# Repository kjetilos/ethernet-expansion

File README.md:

# ethernet-expansion
An ethernet expansion board using the enc28j60 chip

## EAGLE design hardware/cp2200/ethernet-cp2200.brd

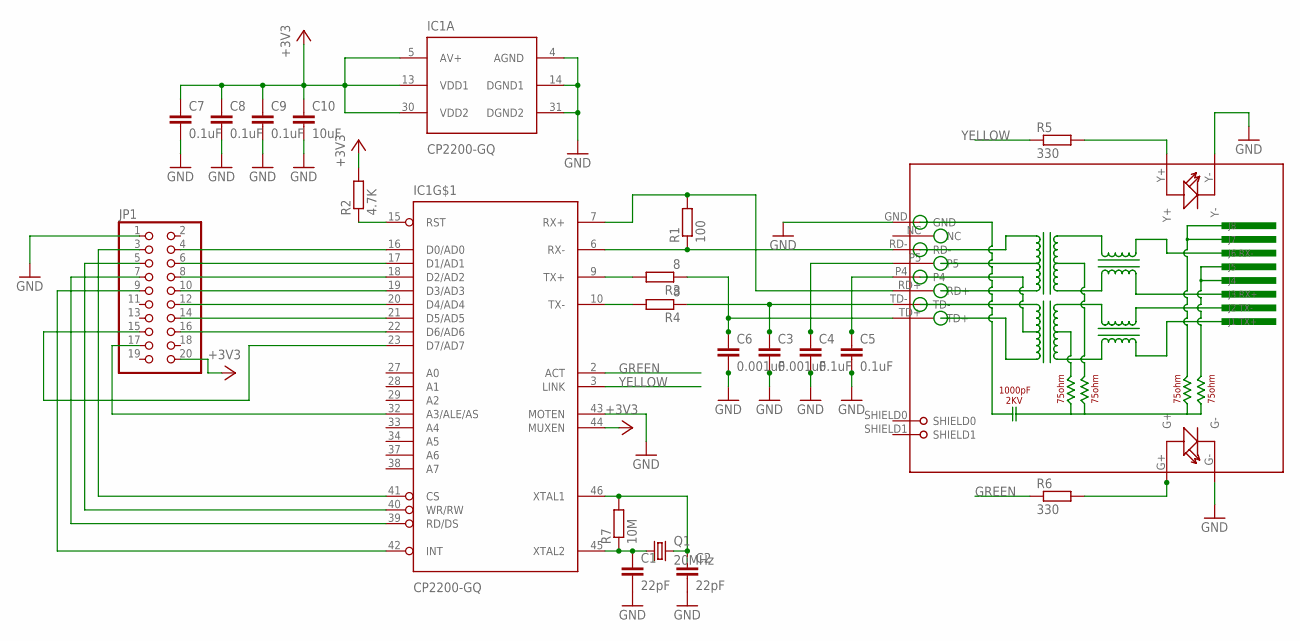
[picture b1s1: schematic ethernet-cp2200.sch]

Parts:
C1, C2: 22pF; C0805
C3, C6: 0.001uF; C0805
C4, C5, C7, C8, C9: 0.1uF; C0805
C10: 10uF; C0805
IC1: CP2200-GQ; TQFP-48
JP1: PINHD-2X10; 2X10
Q1: 20MHz; HC49/S
R1: 100; M0805
R2: 4.7K; M0805
R3, R4: 8; M0805
R5, R6: 330; M0805
R7: 10M; M0805
RJ1: HR911105A

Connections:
+3V3: C7.1, C8.1, C9.1, C10.1, IC1.5 (AV+), IC1.13 (VDD1), IC1.30 (VDD2), IC1.44 (MUXEN), JP1.20, R2.2
GND: C1.2, C2.2, C3.2, C4.2, C5.2, C6.2, C7.2, C8.2, C9.2, C10.2, IC1.4 (AGND), IC1.14 (DGND1), IC1.31 (DGND2), IC1.43 (MOTEN), JP1.1, RJ1.G-, RJ1.GND, RJ1.Y-
GREEN: IC1.2 (ACT), R6.1
unnamed: C2.1, IC1.46 (XTAL1), Q1.2, R7.2
unnamed: C1.1, IC1.45 (XTAL2), Q1.1, R7.1
unnamed: IC1.6 (RX-), R1.1, RJ1.RD-
unnamed: IC1.7 (RX+), R1.2, RJ1.RD+
unnamed: IC1.9 (TX+), R3.2
unnamed: C6.1, R3.1, RJ1.TD+
unnamed: IC1.10 (TX-), R4.2
unnamed: R5.2, RJ1.Y+
unnamed: R6.2, RJ1.G+
unnamed: IC1.32 (A3/ALE/AS), JP1.17
unnamed: C3.1, R4.1, RJ1.TD-
unnamed: IC1.16 (D0/AD0), JP1.4
unnamed: C5.1, RJ1.P4
unnamed: C4.1, RJ1.P5
unnamed: IC1.17 (D1/AD1), JP1.6
unnamed: IC1.18 (D2/AD2), JP1.8
unnamed: IC1.19 (D3/AD3), JP1.10
unnamed: IC1.20 (D4/AD4), JP1.12
unnamed: IC1.21 (D5/AD5), JP1.14
unnamed: IC1.22 (D6/AD6), JP1.16
unnamed: IC1.23 (D7/AD7), JP1.15
unnamed: IC1.41 (CS), JP1.3
unnamed: IC1.40 (WR/RW), JP1.5
unnamed: IC1.39 (RD/DS), JP1.7
unnamed: IC1.42 (INT), JP1.9
unnamed: IC1.15 (RST), R2.1
YELLOW: IC1.3 (LINK), R5.1

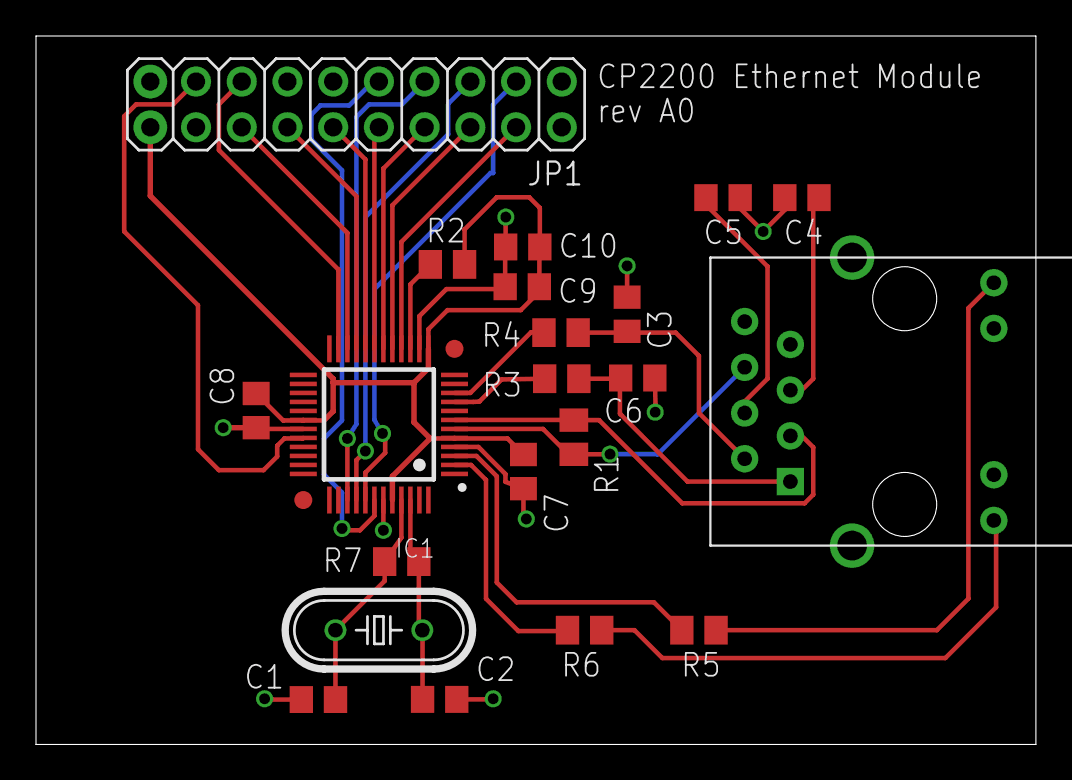
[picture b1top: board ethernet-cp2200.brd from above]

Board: 2 copper layers, 55.5 x 39.4 mm, 21 parts (0 on the bottom side), 30 nets.

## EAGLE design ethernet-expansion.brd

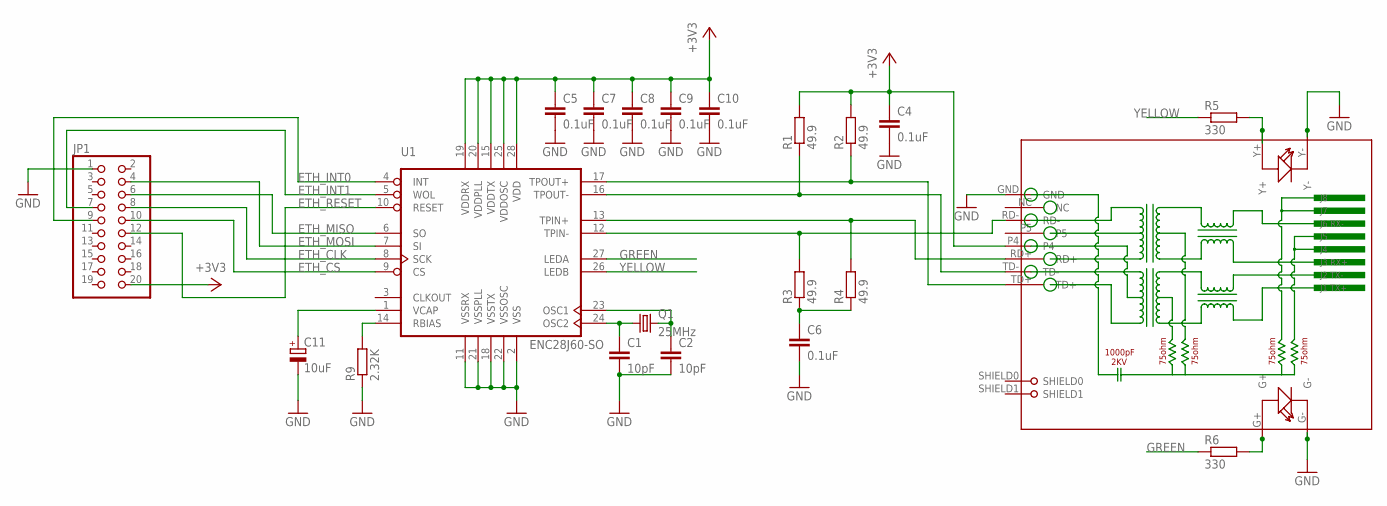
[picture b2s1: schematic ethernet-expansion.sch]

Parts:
C1, C2: 10pF; C0805
C4, C5, C6, C7, C8, C9, C10: 0.1uF; C0805
C11: 10uF; E2-4
JP1: PINHD-2X10; 2X10
Q1: 25MHz; HC49/S
R1, R2, R3, R4: 49.9; M0805
R5, R6: 330; M0805
R9: 2.32K; M0805
RJ1: HR911105A
U1: ENC28J60-SO; SO28W

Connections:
+3V3: C4.1, C5.1, C7.1, C8.1, C9.1, C10.1, JP1.20, R1.2, R2.2, RJ1.P4, U1.15 (VDDTX), U1.19 (VDDRX), U1.20 (VDDPLL), U1.25 (VDDOSC), U1.28 (VDD)
ETH_CLK: JP1.8, U1.8 (SCK)
ETH_CS: JP1.10, U1.9 (CS)
ETH_INT0: JP1.9, U1.4 (INT)
ETH_INT1: JP1.7, U1.5 (WOL)
ETH_MISO: JP1.6, U1.6 (SO)
ETH_MOSI: JP1.4, U1.7 (SI)
ETH_RESET: JP1.12, U1.10 (RESET)
GND: C1.2, C2.2, C4.2, C5.2, C6.2, C7.2, C8.2, C9.2, C10.2, C11.-, JP1.1, R9.1, RJ1.G-, RJ1.GND, RJ1.Y-, U1.2 (VSS), U1.11 (VSSRX), U1.18 (VSSTX), U1.21 (VSSPLL), U1.22 (VSSOSC)
GREEN: R6.1, U1.27 (LEDA)
unnamed: C6.1, R3.1, R4.1
unnamed: R5.2, RJ1.Y+
unnamed: R6.2, RJ1.G+
unnamed: C1.1, Q1.1, U1.24 (OSC2)
unnamed: C2.1, Q1.2, U1.23 (OSC1)
unnamed: R9.2, U1.14 (RBIAS)
unnamed: C11.+, U1.1 (VCAP)
TPIN_N: R3.2, RJ1.RD-, U1.12 (TPIN-)
TPIN_P: R4.2, RJ1.RD+, U1.13 (TPIN+)
TPOUT_N: R1.1, RJ1.TD-, U1.16 (TPOUT-)
TPOUT_P: R2.1, RJ1.TD+, U1.17 (TPOUT+)
YELLOW: R5.1, U1.26 (LEDB)

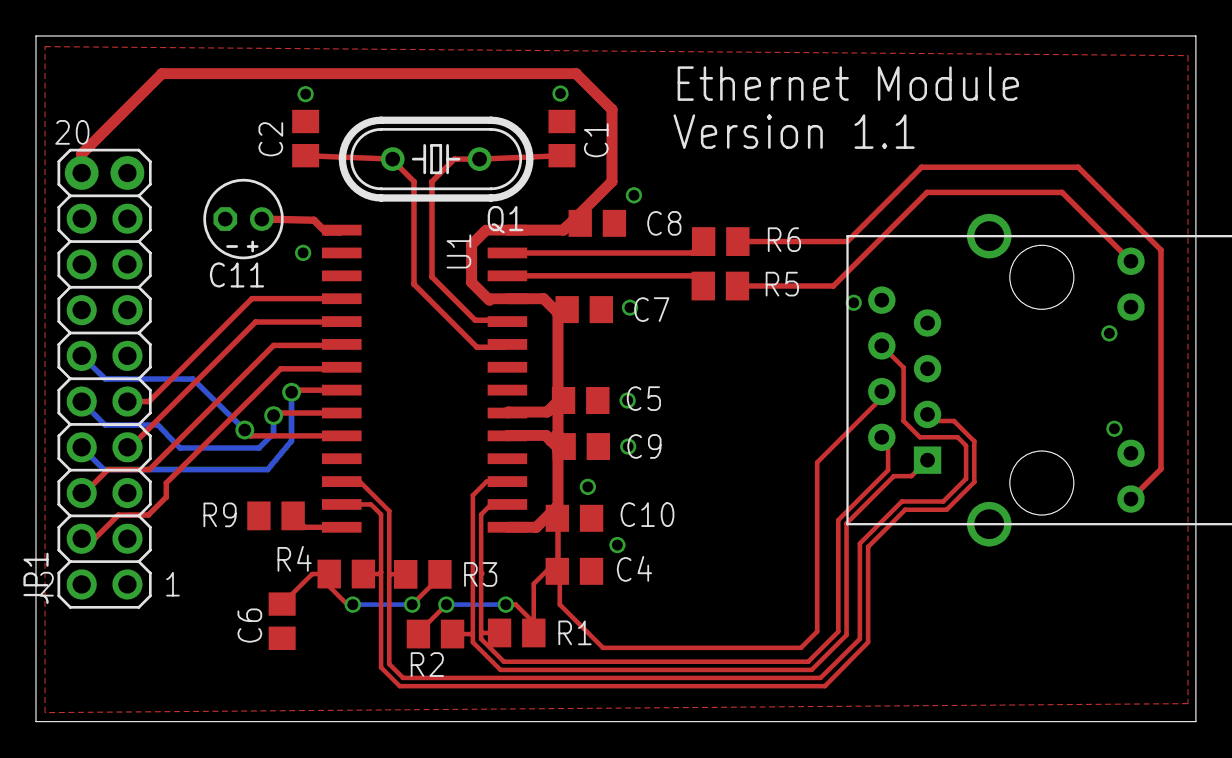
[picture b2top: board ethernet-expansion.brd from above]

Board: 2 copper layers, 64.4 x 38.1 mm, 21 parts (0 on the bottom side), 22 nets.

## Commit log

2015-08-04 Adding the initial schematic and board layout
2015-08-04 Adding notes and gitignore
2015-08-29 Add center tap connection and interrupt connections
2015-09-01 Started to route the connector
2015-09-02 Initial board with all wires routed
2015-09-02 Adding some text
2015-09-02 Rotated oscillator to get a better Vdd trace
2015-09-05 Adding ground fill on top layer and trying out other placements
2015-09-05 Canged signal trace with from 0.1 to 0.3
2015-09-06 Routed differential pairs and fixed most of the drc errors
2015-09-06 Added some silk screen and added osh park eagle design rule file
2015-09-06 Recreated the ground fill to fix the last error
2015-09-07 Adding dru and cam file from Seeed studio and moving traces to make the ground fill more complete
2015-09-10 Adding ground plane on bottom layer and vias at ground points
2015-10-03 Swapping header pin rows to make it correct, and adding debug uart pins
2015-10-03 Adding image of board and schematic
2015-10-29 Adding software for the ethernet expansion card
2015-10-29 Moving stk specific config to another folder
2015-11-08 Adding support for blocking socket operations and support for frames divided into multiple pbuf's
2015-11-09 Adding support for displaying a text on the STK3700 lcd display
2016-01-04 Adding board and schematic for cp2200 based design
2016-01-26 Connected the cp2200 board
2016-01-26 Updated board after drc
2016-01-28 Fixing smd pad width and some wire traces and adding text
2017-07-09 Updated cp2200 schematic
    Added pictures of the schematic and board
2017-07-09 Added slsproj files for STK3700 and STK3600
    This will make the projects easy to import into Simplicity Studio. This
    also removes the need to have FreeRTOS bundled inside the git repo since
    it's linked to the version inside the MCU SDK.
2017-07-09 Renamed root software folder.
    The project is not stk3700 specific so i renamed the folder.
2017-07-09 Removed FreeRTOS from the project
    FreeRTOS is no longer needed in the project since it is linked in from
    the MCU SDK inside of Studio. The version in studio is FreeRTOS 9.0.0.
2017-07-09 Added a hardware folder for all the schematic and board work
2017-07-14 Adding swo debug output to the project.
2017-07-14 Adding retarget vcom to STK3700 project.
    Using VCOM as debug output port. SWO would be the ideal setup but it is
    not smooth enough to use. STK3600 looks like it's missing retarget vcom
    functionality.

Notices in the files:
parts and their libraries:
SparkFun-Connectors: Licensing: Creative Commons ShareAlike 4.0 International - https://creativecommons.org/licenses/by-sa/4.0
